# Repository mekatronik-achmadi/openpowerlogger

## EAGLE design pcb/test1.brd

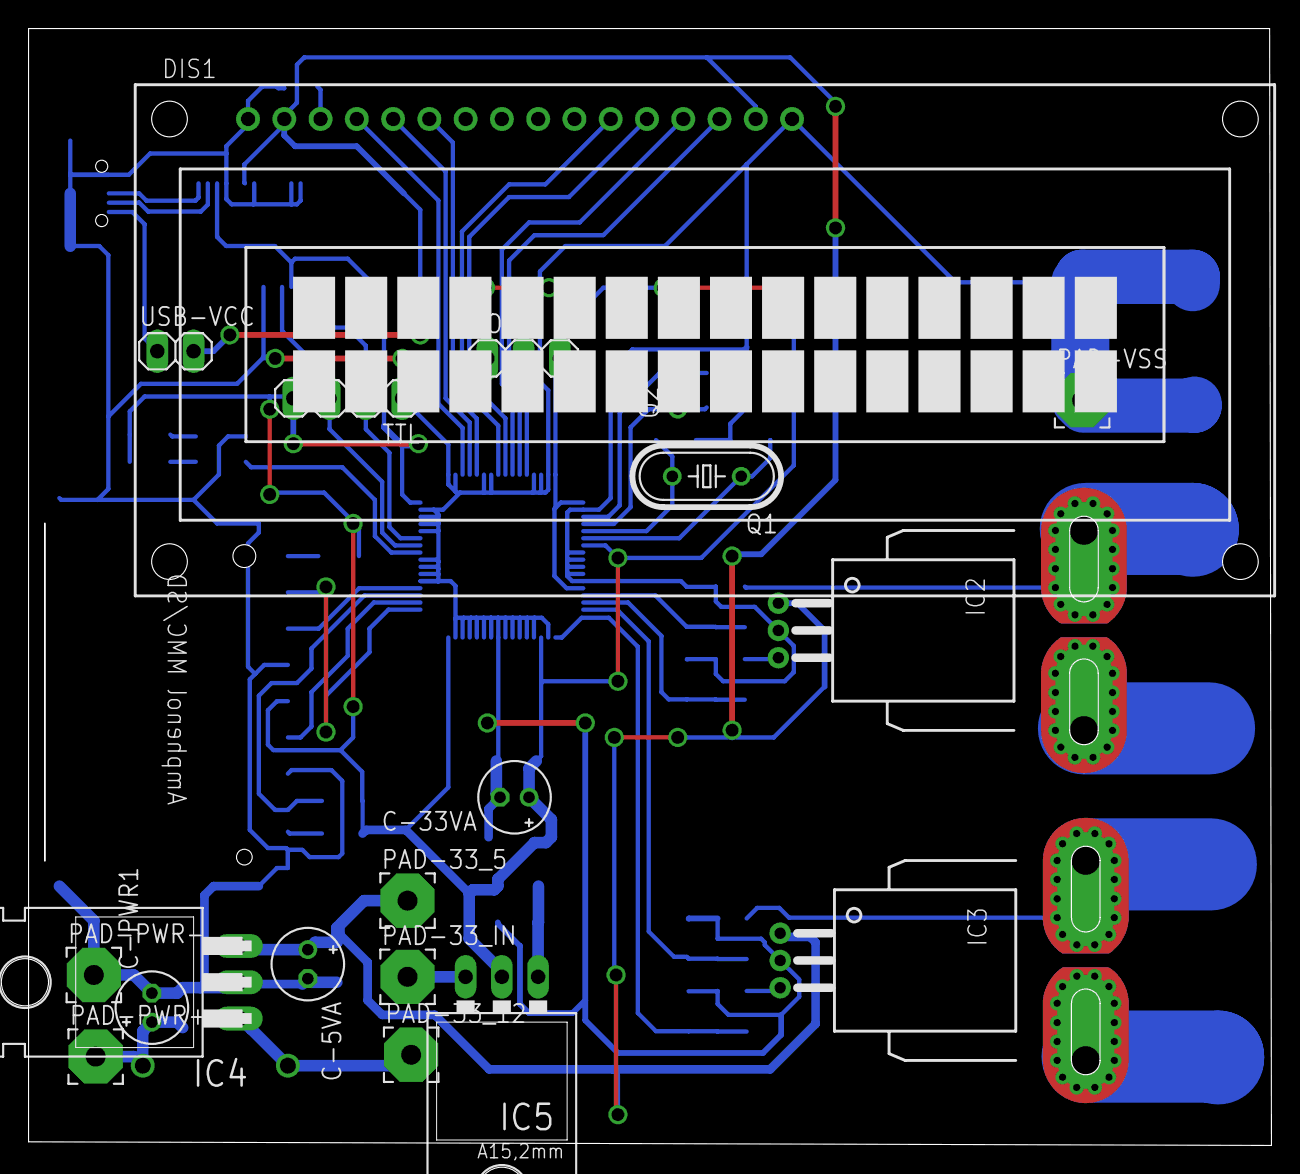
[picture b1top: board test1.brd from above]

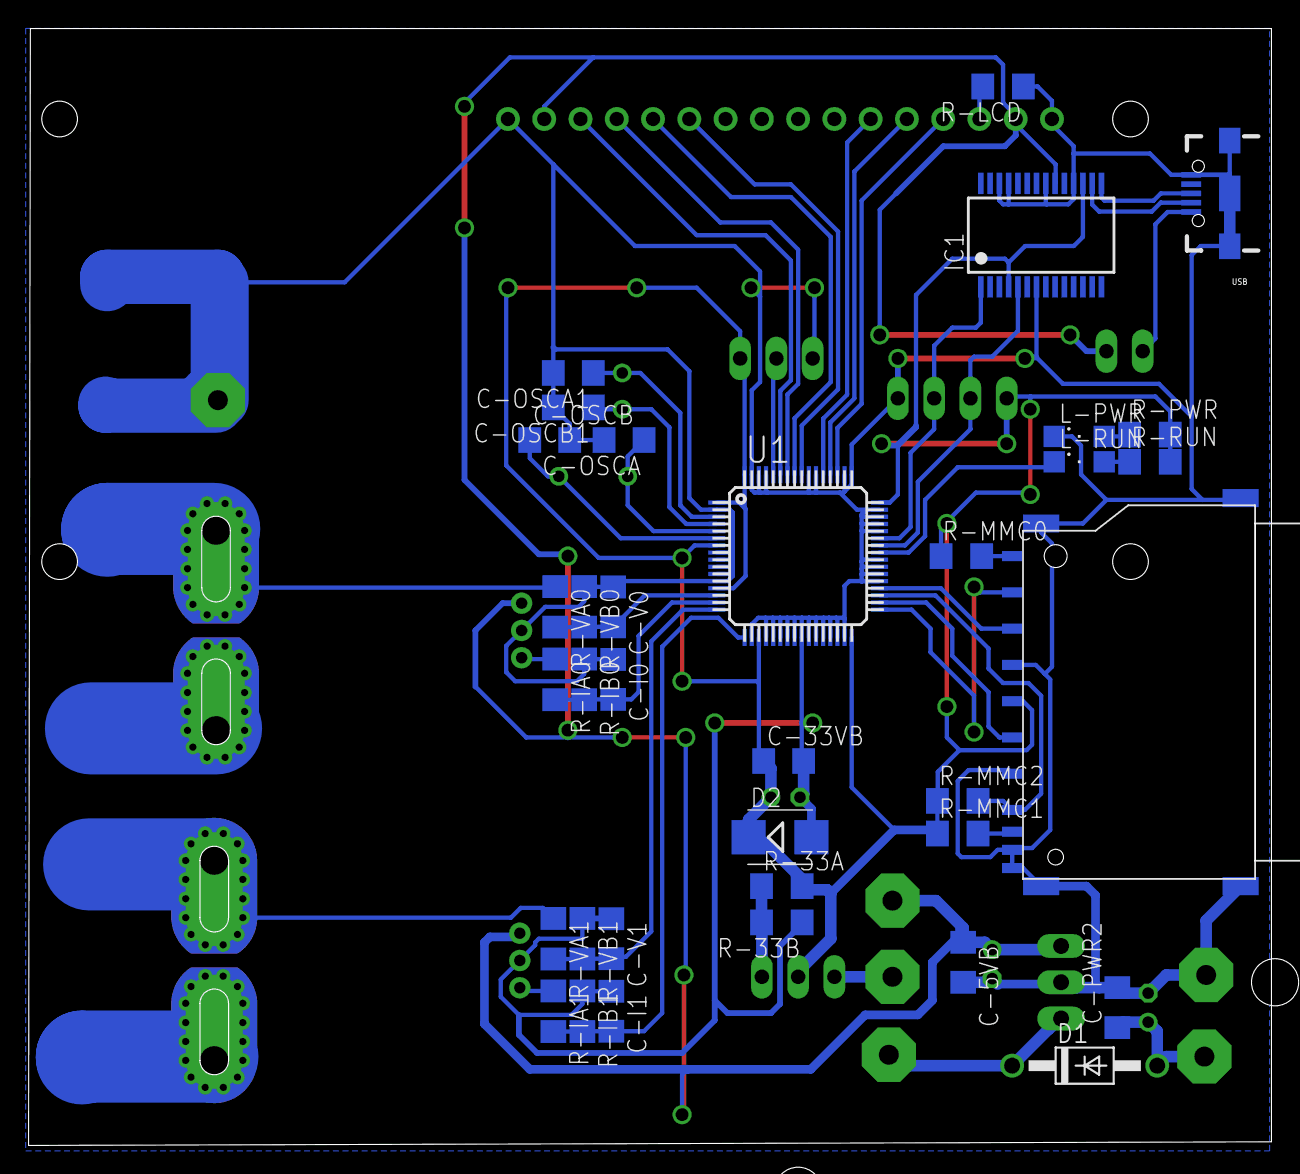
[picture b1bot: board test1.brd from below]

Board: 2 copper layers, 87.0 x 78.2 mm, 54 parts (35 on the bottom side), 42 nets.

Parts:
BOOT: 1X03
C-5VA, C-33VA: 1000uf/25v; E2-5
C-5VB, C-33VB: 22pf; C1206
C-I0, C-I1: 100nf; C1206
C-OSCA, C-OSCA1: 22pf; C1206
C-OSCB, C-OSCB1: 22pf; C1206
C-PWR1: 1000uf/25v; E2-5
C-PWR2: 22pf; C1206
C-V0, C-V1: 100nf; C1206
D1: 1N4004; DO41-10
D2: 3v6; SMB
DIS1: TUXGR_16X2_R2
IC1: FT232RL; SSOP28
IC2, IC3: ACS758ECB-200B-PFF-T; CB-PFF
IC4: 7805T; TO220H
IC5: LM1117; 317TL
J1: SDCMF-10915W010
L-PWR: SML1206
L-RUN: SML1206
PAD-33_5, PAD-33_12, PAD-33_IN: 3,81/1,4
PAD-PWR+: 3,81/1,4
PAD-PWR-: 3,81/1,4
PAD-VSS: 3,81/1,4
Q1: 8mhz; HC49/S
Q2: 32khz; TC26V
R-33A: 270; R1206
R-33B: 330; R1206
R-IA0, R-IA1: 4k7; R1206
R-IB0, R-IB1: 4k7; R1206
R-LCD: 560; R1206
R-MMC0, R-MMC1, R-MMC2: 10k; R1206
R-PWR: 330; R1206
R-RUN: 330; R1206
R-VA0, R-VA1: 4k7; R1206
R-VB0, R-VB1: 4k7; R1206
TTL: 1X04
U1: STM32F10XRXT6; TQFP64
USB: USB_MICROB_PLUGCONN-11752; USB-B-MICRO-SMD_V03
USB-VCC: 1X02

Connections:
D4: DIS1.11, U1.56
D5: DIS1.12, U1.57
D6: DIS1.13, U1.58
D7: DIS1.14, U1.59
EN: DIS1.6, U1.53
I0: C-I0.2, R-IA0.2, R-IB0.2, U1.15
I1: C-I1.2, R-IA1.2, R-IB1.2, U1.17
MISO: J1.7, R-MMC2.2, U1.35
MOSI: J1.2, U1.36
unnamed: IC1.16, USB.D-1
unnamed: IC1.15, USB.D+1
unnamed: IC2.3, R-IA0.1
unnamed: IC2.IP-, IC2.IP-@2, IC2.IP-@3, IC2.IP-@4, IC2.IP-@5, IC2.IP-@6, IC2.IP-@7, IC2.IP-@8, IC2.IP-@9, IC2.IP-@10, IC2.IP-@11, IC2.IP-@12, IC2.IP-@13, IC2.IP-@14, IC2.IP-@15, IC2.IP-@16, IC2.IP-@17, R-VA0.1
unnamed: USB.VBUS1, USB-VCC.1
unnamed: IC3.3, R-IA1.1
unnamed: IC3.IP-, IC3.IP-@2, IC3.IP-@3, IC3.IP-@4, IC3.IP-@5, IC3.IP-@6, IC3.IP-@7, IC3.IP-@8, IC3.IP-@9, IC3.IP-@10, IC3.IP-@11, IC3.IP-@12, IC3.IP-@13, IC3.IP-@14, IC3.IP-@15, IC3.IP-@16, IC3.IP-@17, R-VA1.1
unnamed: DIS1.3, R-LCD.2
unnamed: L-PWR.A, R-PWR.1
unnamed: L-RUN.A, R-RUN.1
unnamed: C-PWR1.+, C-PWR2.1, D1.A, PAD-PWR+.1
unnamed: IC5.3, PAD-33_IN.1
unnamed: IC5.1, R-33A.1, R-33B.2
unnamed: BOOT.2, U1.60
unnamed: J1.8, R-MMC1.2
unnamed: J1.9, R-MMC0.2
NSS: J1.1, U1.33
OSC32A: C-OSCA1.1, Q2.2, U1.3
OSC32B: C-OSCB1.1, Q2.1, U1.4
OSCA: C-OSCA.1, Q1.2, U1.5
OSCB: C-OSCB.1, Q1.1, U1.6
RS: DIS1.4, U1.51
RUN: L-RUN.C, U1.41
RW: DIS1.5, U1.52
RX: IC1.1, TTL.2, U1.43
SCK: J1.5, U1.34
TX: IC1.5, TTL.3, U1.42
V0: C-V0.2, R-VA0.2, R-VB0.2, U1.14
V1: C-V1.2, R-VA1.2, R-VB1.2, U1.16
V12: D1.C, IC4.1, PAD-33_12.1
VCC: C-5VA.+, C-5VB.1, DIS1.2, DIS1.15, IC1.20, IC2.1, IC3.1, IC4.3, PAD-33_5.1, USB-VCC.2
VDD: BOOT.3, C-33VA.+, C-33VB.1, D2.C, IC1.4, IC1.17, IC5.2, J1.4, R-33A.2, R-MMC0.1, R-MMC1.1, R-MMC2.1, R-PWR.2, R-RUN.2, TTL.4, U1.1, U1.7, U1.13, U1.19, U1.32, U1.48, U1.64
VSS: BOOT.1, C-5VA.-, C-5VB.2, C-33VA.-, C-33VB.2, C-I0.1, C-I1.1, C-OSCA.2, C-OSCA1.2, C-OSCB.2, C-OSCB1.2, C-PWR1.-, C-PWR2.2, C-V0.1, C-V1.1, D2.A, DIS1.1, DIS1.16, IC1.7, IC1.18, IC1.21, IC1.25, IC1.26, IC2.2, IC3.2, IC4.2, J1.3, J1.6, J1.10, J1.11, J1.M1, J1.M2, J1.M3, J1.M4, L-PWR.C, PAD-PWR-.1, PAD-VSS.1, R-33B.1, R-IB0.1, R-IB1.1, R-LCD.1, R-VB0.1, R-VB1.1, TTL.1, U1.2, U1.8, U1.9, U1.10, U1.11, U1.12, U1.18, U1.20, U1.21, U1.22, U1.23, U1.24, U1.25, U1.26, U1.27, U1.28, U1.29, U1.30, U1.31, U1.37, U1.38, U1.39, U1.40, U1.44, U1.45, U1.46, U1.47, U1.49, U1.50, U1.54, U1.55, U1.61, U1.62, U1.63, USB.GND1, USB.SHIELD1, USB.SHIELD2, USB.SHIELD3

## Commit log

2015-01-27 skematik dulu
2015-01-27 coba board
2015-01-28 ready to manufactured and trial
2015-02-21 start work on firmware
2015-02-21 disable JTAG for GPIO on PB4, PB5, PA13, PA14, PA15
2015-02-21 Alphanumeric LCD Works
2015-02-22 FatFS bikin gila
2015-02-22 fatFS works
2015-02-22 f_write gunakan buffer 16 byte. Tinggal Float Value
2015-02-22 ADC ok
2015-02-22 FLOAT Value Works
2015-02-22 Tinggal Kalibrasi dan QC
2015-02-22 ready to test
2015-02-23 offset value use variable not macro
2015-02-23 revisi offset
2015-04-29 revisi layout
2015-05-12 Calibrated & Ready to test
2015-05-18 save in CSV format
2015-05-29 Pengujian di Unnes
2015-05-29 Interface added
2015-07-11 docs start
2015-07-11 progress document
2015-07-12 document finish
2015-07-12 ready to publish
2015-07-13 revisi and ready to publish
2015-07-13 revisi

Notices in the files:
parts and their libraries:
SparkFun-Connectors: Licensing: Creative Commons ShareAlike 4.0 International - https://creativecommons.org/licenses/by-sa/4.0
